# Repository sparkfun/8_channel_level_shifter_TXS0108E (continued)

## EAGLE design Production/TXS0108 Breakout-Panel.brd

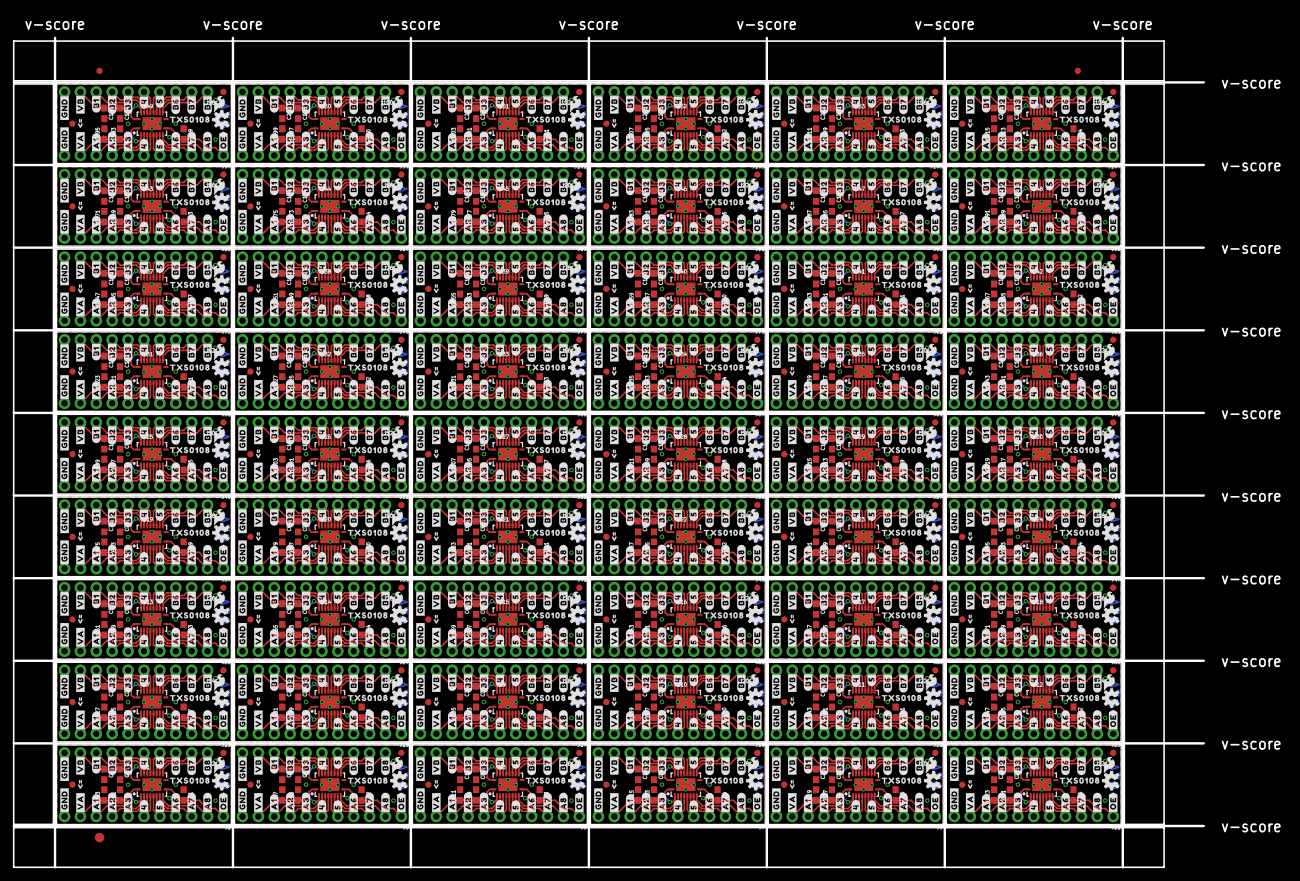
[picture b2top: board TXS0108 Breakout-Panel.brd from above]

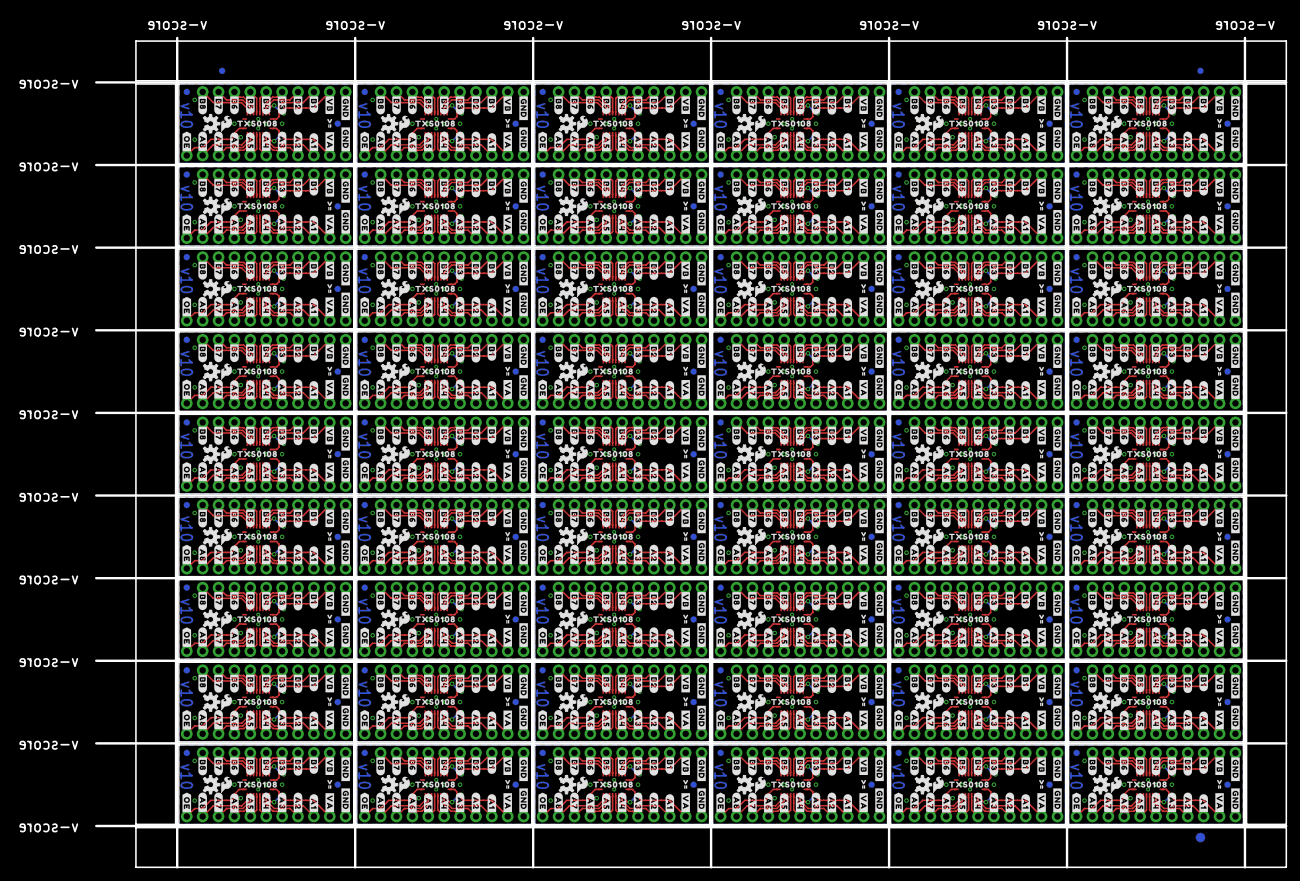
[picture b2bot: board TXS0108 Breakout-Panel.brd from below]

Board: 2 copper layers, 190.2 x 132.6 mm, 3462 parts (1515 on the bottom side), 1080 nets.

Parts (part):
C1, C2, C5, C6, C9, C10, C13, C14, C17, C18, C21, C22, C25, C26, C29, C30, C33, C34, C37, C38, C41, C42, C45, C46, C49, C50, C53, C54, C57, C58, C61, C62, C65, C66, C69, C70, C73, C74, C77, C78, C81, C82, C85, C86, C89, C90, C93, C94, C97, C98, C101, C102, C105, C106, C109, C110, C113, C114, C117, C118, C121, C122, C125, C126, C129, C130, C133, C134, C137, C138, C141, C142, C145, C146, C149, C150, C153, C154, C157, C158, C161, C162, C165, C166, C169, C170, C173, C174, C177, C178, C181, C182, C185, C186, C189, C190, C193, C194, C197, C198, C201, C202, C205, C206, C209, C210, C213, C214: 0.1uF; 0603
C3, C4, C7, C8, C11, C12, C15, C16, C19, C20, C23, C24, C27, C28, C31, C32, C35, C36, C39, C40, C43, C44, C47, C48, C51, C52, C55, C56, C59, C60, C63, C64, C67, C68, C71, C72, C75, C76, C79, C80, C83, C84, C87, C88, C91, C92, C95, C96, C99, C100, C103, C104, C107, C108, C111, C112, C115, C116, C119, C120, C123, C124, C127, C128, C131, C132, C135, C136, C139, C140, C143, C144, C147, C148, C151, C152, C155, C156, C159, C160, C163, C164, C167, C168, C171, C172, C175, C176, C179, C180, C183, C184, C187, C188, C191, C192, C195, C196, C199, C200, C203, C204, C207, C208, C211, C212, C215, C216: 10uF; 0603
E$1, E$2, E$3, E$4: FIDUCIAL-1X2
E$5, E$6: FIDUCIAL-1.5X3
FD1, FD2, FD3, FD4, FD5, FD6, FD7, FD8, FD9, FD10, FD11, FD12, FD13, FD14, FD15, FD16, FD17, FD18, FD19, FD20, FD21, FD22, FD23, FD24, FD25, FD26, FD27, FD28, FD29, FD30, FD31, FD32, FD33, FD34, FD35, FD36, FD37, FD38, FD39, FD40, FD41, FD42, FD43, FD44, FD45, FD46, FD47, FD48, FD49, FD50, FD51, FD52, FD53, FD54, FD55, FD56, FD57, FD58, FD59, FD60, FD61, FD62, FD63, FD64, FD65, FD66, FD67, FD68, FD69, FD70, FD71, FD72, FD73, FD74, FD75, FD76, FD77, FD78, FD79, FD80, FD81, FD82, FD83, FD84, FD85, FD86, FD87, FD88, FD89, FD90, FD91, FD92, FD93, FD94, FD95, FD96, FD97, FD98, FD99, FD100, FD101, FD102, FD103, FD104, FD105, FD106, FD107, FD108, FD109, FD110, FD111, FD112, FD113, FD114, FD115, FD116, FD117, FD118, FD119, FD120, FD121, FD122, FD123, FD124, FD125, FD126, FD127, FD128, FD129, FD130, FD131, FD132, FD133, FD134, FD135, FD136, FD137, FD138, FD139, FD140, FD141, FD142, FD143, FD144, FD145, FD146, FD147, FD148, FD149, FD150, FD151, FD152, FD153, FD154, FD155, FD156, FD157, FD158, FD159, FD160, FD161, FD162, FD163, FD164, FD165, FD166, FD167, FD168, FD169, FD170, FD171, FD172, FD173, FD174, FD175, FD176, FD177, FD178, FD179, FD180, FD181, FD182, FD183, FD184, FD185, FD186, FD187, FD188, FD189, FD190, FD191, FD192, FD193, FD194, FD195, FD196, FD197, FD198, FD199, FD200, FD201, FD202, FD203, FD204, FD205, FD206, FD207, FD208, FD209, FD210, FD211, FD212, FD213, FD214, FD215, FD216: FIDUCIAL1X2; FIDUCIAL-1X2
J1, J3, J5, J7, J9, J11, J13, J15, J17, J19, J21, J23, J25, J27, J29, J31, J33, J35, J37, J39, J41, J43, J45, J47, J49, J51, J53, J55, J57, J59, J61, J63, J65, J67, J69, J71, J73, J75, J77, J79, J81, J83, J85, J87, J89, J91, J93, J95, J97, J99, J101, J103, J105, J107: 1X11_NO_SILK
J2, J4, J6, J8, J10, J12, J14, J16, J18, J20, J22, J24, J26, J28, J30, J32, J34, J36, J38, J40, J42, J44, J46, J48, J50, J52, J54, J56, J58, J60, J62, J64, J66, J68, J70, J72, J74, J76, J78, J80, J82, J84, J86, J88, J90, J92, J94, J96, J98, J100, J102, J104, J106, J108: 1X10_NO_SILK
LOGO1, LOGO4, LOGO5, LOGO8, LOGO9, LOGO12, LOGO13, LOGO16, LOGO17, LOGO20, LOGO21, LOGO24, LOGO25, LOGO28, LOGO29, LOGO32, LOGO33, LOGO36, LOGO37, LOGO40, LOGO41, LOGO44, LOGO45, LOGO48, LOGO49, LOGO52, LOGO53, LOGO56, LOGO57, LOGO60, LOGO61, LOGO64, LOGO65, LOGO68, LOGO69, LOGO72, LOGO73, LOGO76, LOGO77, LOGO80, LOGO81, LOGO84, LOGO85, LOGO88, LOGO89, LOGO92, LOGO93, LOGO96, LOGO97, LOGO100, LOGO101, LOGO104, LOGO105, LOGO108, LOGO109, LOGO112, LOGO113, LOGO116, LOGO117, LOGO120, LOGO121, LOGO124, LOGO125, LOGO128, LOGO129, LOGO132, LOGO133, LOGO136, LOGO137, LOGO140, LOGO141, LOGO144, LOGO145, LOGO148, LOGO149, LOGO152, LOGO153, LOGO156, LOGO157, LOGO160, LOGO161, LOGO164, LOGO165, LOGO168, LOGO169, LOGO172, LOGO173, LOGO176, LOGO177, LOGO180, LOGO181, LOGO184, LOGO185, LOGO188, LOGO189, LOGO192, LOGO193, LOGO196, LOGO197, LOGO200, LOGO201, LOGO204, LOGO205, LOGO208, LOGO209, LOGO212, LOGO213, LOGO216: OSHW-LOGOS; OSHW-LOGO-S
LOGO2, LOGO3, LOGO6, LOGO7, LOGO10, LOGO11, LOGO14, LOGO15, LOGO18, LOGO19, LOGO22, LOGO23, LOGO26, LOGO27, LOGO30, LOGO31, LOGO34, LOGO35, LOGO38, LOGO39, LOGO42, LOGO43, LOGO46, LOGO47, LOGO50, LOGO51, LOGO54, LOGO55, LOGO58, LOGO59, LOGO62, LOGO63, LOGO66, LOGO67, LOGO70, LOGO71, LOGO74, LOGO75, LOGO78, LOGO79, LOGO82, LOGO83, LOGO86, LOGO87, LOGO90, LOGO91, LOGO94, LOGO95, LOGO98, LOGO99, LOGO102, LOGO103, LOGO106, LOGO107, LOGO110, LOGO111, LOGO114, LOGO115, LOGO118, LOGO119, LOGO122, LOGO123, LOGO126, LOGO127, LOGO130, LOGO131, LOGO134, LOGO135, LOGO138, LOGO139, LOGO142, LOGO143, LOGO146, LOGO147, LOGO150, LOGO151, LOGO154, LOGO155, LOGO158, LOGO159, LOGO162, LOGO163, LOGO166, LOGO167, LOGO170, LOGO171, LOGO174, LOGO175, LOGO178, LOGO179, LOGO182, LOGO183, LOGO186, LOGO187, LOGO190, LOGO191, LOGO194, LOGO195, LOGO198, LOGO199, LOGO202, LOGO203, LOGO206, LOGO207, LOGO210, LOGO211, LOGO214, LOGO215: SFE_LOGO_FLAME.1_INCH; SFE_LOGO_FLAME_.1
R1, R2, R3, R4, R5, R6, R7, R8, R9, R10, R11, R12, R13, R14, R15, R16, R17, R18, R19, R20, R21, R22, R23, R24, R25, R26, R27, R28, R29, R30, R31, R32, R33, R34, R35, R36, R37, R38, R39, R40, R41, R42, R43, R44, R45, R46, R47, R48, R49, R50, R51, R52, R53, R54: 100k; 0603
U1, U2, U3, U4, U5, U6, U7, U8, U9, U10, U11, U12, U13, U14, U15, U16, U17, U18, U19, U20, U21, U22, U23, U24, U25, U26, U27, U28, U29, U30, U31, U32, U33, U34, U35, U36, U37, U38, U39, U40, U41, U42, U43, U44, U45, U46, U47, U48, U49, U50, U51, U52, U53, U54: TXS0108; VFQFN-20
U$1, U$2, U$32, U$34, U$49, U$50, U$56, U$57, U$97, U$98, U$104, U$105, U$145, U$146, U$152, U$153, U$193, U$194, U$200, U$201, U$241, U$242, U$248, U$249, U$289, U$290, U$296, U$297, U$337, U$338, U$344, U$345, U$385, U$386, U$392, U$393, U$433, U$434, U$440, U$441, U$481, U$482, U$488, U$489, U$529, U$530, U$536, U$537, U$577, U$578, U$584, U$585, U$625, U$626, U$632, U$633, U$673, U$674, U$680, U$681, U$721, U$722, U$728, U$729, U$769, U$770, U$776, U$777, U$817, U$818, U$824, U$825, U$865, U$866, U$872, U$873, U$913, U$914, U$920, U$921, U$961, U$962, U$968, U$969, U$1009, U$1010, U$1016, U$1017, U$1057, U$1058, U$1064, U$1065, U$1105, U$1106, U$1112, U$1113, U$1153, U$1154, U$1160, U$1161, U$1201, U$1202, U$1208, U$1209, U$1249, U$1250, U$1256, U$1257, U$1297, U$1298, U$1304, U$1305, U$1345, U$1346, U$1352, U$1353, U$1393, U$1394, U$1400, U$1401, U$1441, U$1442, U$1448, U$1449, U$1489, U$1490, U$1496, U$1497, U$1537, U$1538, U$1544, U$1545, U$1585, U$1586, U$1592, U$1593, U$1633, U$1634, U$1640, U$1641, U$1681, U$1682, U$1688, U$1689, U$1729, U$1730, U$1736, U$1737, U$1777, U$1778, U$1784, U$1785, U$1825, U$1826, U$1832, U$1833, U$1873, U$1874, U$1880, U$1881, U$1921, U$1922, U$1928, U$1929, U$1969, U$1970, U$1976, U$1977, U$2017, U$2018, U$2024, U$2025, U$2065, U$2066, U$2072, U$2073, U$2113, U$2114, U$2120, U$2121, U$2161, U$2162, U$2168, U$2169, U$2209, U$2210, U$2216, U$2217, U$2257, U$2258, U$2264, U$2265, U$2305, U$2306, U$2312, U$2313, U$2353, U$2354, U$2360, U$2361, U$2401, U$2402, U$2408, U$2409, U$2449, U$2450, U$2456, U$2457, U$2497, U$2498, U$2504, U$2505, U$2545, U$2546, U$2552, U$2553: #GND#0
U$3, U$4, U$52, U$53, U$100, U$101, U$148, U$149, U$196, U$197, U$244, U$245, U$292, U$293, U$340, U$341, U$388, U$389, U$436, U$437, U$484, U$485, U$532, U$533, U$580, U$581, U$628, U$629, U$676, U$677, U$724, U$725, U$772, U$773, U$820, U$821, U$868, U$869, U$916, U$917, U$964, U$965, U$1012, U$1013, U$1060, U$1061, U$1108, U$1109, U$1156, U$1157, U$1204, U$1205, U$1252, U$1253, U$1300, U$1301, U$1348, U$1349, U$1396, U$1397, U$1444, U$1445, U$1492, U$1493, U$1540, U$1541, U$1588, U$1589, U$1636, U$1637, U$1684, U$1685, U$1732, U$1733, U$1780, U$1781, U$1828, U$1829, U$1876, U$1877, U$1924, U$1925, U$1972, U$1973, U$2020, U$2021, U$2068, U$2069, U$2116, U$2117, U$2164, U$2165, U$2212, U$2213, U$2260, U$2261, U$2308, U$2309, U$2356, U$2357, U$2404, U$2405, U$2452, U$2453, U$2500, U$2501, U$2548, U$2549: #VA#0
U$5, U$60, U$108, U$156, U$204, U$252, U$300, U$348, U$396, U$444, U$492, U$540, U$588, U$636, U$684, U$732, U$780, U$828, U$876, U$924, U$972, U$1020, U$1068, U$1116, U$1164, U$1212, U$1260, U$1308, U$1356, U$1404, U$1452, U$1500, U$1548, U$1596, U$1644, U$1692, U$1740, U$1788, U$1836, U$1884, U$1932, U$1980, U$2028, U$2076, U$2124, U$2172, U$2220, U$2268, U$2316, U$2364, U$2412, U$2460, U$2508, U$2556: #A1#0
U$6, U$61, U$109, U$157, U$205, U$253, U$301, U$349, U$397, U$445, U$493, U$541, U$589, U$637, U$685, U$733, U$781, U$829, U$877, U$925, U$973, U$1021, U$1069, U$1117, U$1165, U$1213, U$1261, U$1309, U$1357, U$1405, U$1453, U$1501, U$1549, U$1597, U$1645, U$1693, U$1741, U$1789, U$1837, U$1885, U$1933, U$1981, U$2029, U$2077, U$2125, U$2173, U$2221, U$2269, U$2317, U$2365, U$2413, U$2461, U$2509, U$2557: #A2#0
U$7, U$62, U$110, U$158, U$206, U$254, U$302, U$350, U$398, U$446, U$494, U$542, U$590, U$638, U$686, U$734, U$782, U$830, U$878, U$926, U$974, U$1022, U$1070, U$1118, U$1166, U$1214, U$1262, U$1310, U$1358, U$1406, U$1454, U$1502, U$1550, U$1598, U$1646, U$1694, U$1742, U$1790, U$1838, U$1886, U$1934, U$1982, U$2030, U$2078, U$2126, U$2174, U$2222, U$2270, U$2318, U$2366, U$2414, U$2462, U$2510, U$2558: #A3#0
U$8, U$93, U$141, U$189, U$237, U$285, U$333, U$381, U$429, U$477, U$525, U$573, U$621, U$669, U$717, U$765, U$813, U$861, U$909, U$957, U$1005, U$1053, U$1101, U$1149, U$1197, U$1245, U$1293, U$1341, U$1389, U$1437, U$1485, U$1533, U$1581, U$1629, U$1677, U$1725, U$1773, U$1821, U$1869, U$1917, U$1965, U$2013, U$2061, U$2109, U$2157, U$2205, U$2253, U$2301, U$2349, U$2397, U$2445, U$2493, U$2541, U$2589: #4#0
U$9, U$94, U$142, U$190, U$238, U$286, U$334, U$382, U$430, U$478, U$526, U$574, U$622, U$670, U$718, U$766, U$814, U$862, U$910, U$958, U$1006, U$1054, U$1102, U$1150, U$1198, U$1246, U$1294, U$1342, U$1390, U$1438, U$1486, U$1534, U$1582, U$1630, U$1678, U$1726, U$1774, U$1822, U$1870, U$1918, U$1966, U$2014, U$2062, U$2110, U$2158, U$2206, U$2254, U$2302, U$2350, U$2398, U$2446, U$2494, U$2542, U$2590: #5#0
U$10, U$63, U$111, U$159, U$207, U$255, U$303, U$351, U$399, U$447, U$495, U$543, U$591, U$639, U$687, U$735, U$783, U$831, U$879, U$927, U$975, U$1023, U$1071, U$1119, U$1167, U$1215, U$1263, U$1311, U$1359, U$1407, U$1455, U$1503, U$1551, U$1599, U$1647, U$1695, U$1743, U$1791, U$1839, U$1887, U$1935, U$1983, U$2031, U$2079, U$2127, U$2175, U$2223, U$2271, U$2319, U$2367, U$2415, U$2463, U$2511, U$2559: #A6#0
U$11, U$64, U$112, U$160, U$208, U$256, U$304, U$352, U$400, U$448, U$496, U$544, U$592, U$640, U$688, U$736, U$784, U$832, U$880, U$928, U$976, U$1024, U$1072, U$1120, U$1168, U$1216, U$1264, U$1312, U$1360, U$1408, U$1456, U$1504, U$1552, U$1600, U$1648, U$1696, U$1744, U$1792, U$1840, U$1888, U$1936, U$1984, U$2032, U$2080, U$2128, U$2176, U$2224, U$2272, U$2320, U$2368, U$2416, U$2464, U$2512, U$2560: #A7#0
U$12, U$65, U$113, U$161, U$209, U$257, U$305, U$353, U$401, U$449, U$497, U$545, U$593, U$641, U$689, U$737, U$785, U$833, U$881, U$929, U$977, U$1025, U$1073, U$1121, U$1169, U$1217, U$1265, U$1313, U$1361, U$1409, U$1457, U$1505, U$1553, U$1601, U$1649, U$1697, U$1745, U$1793, U$1841, U$1889, U$1937, U$1985, U$2033, U$2081, U$2129, U$2177, U$2225, U$2273, U$2321, U$2369, U$2417, U$2465, U$2513, U$2561: #A8#0
U$13, U$66, U$114, U$162, U$210, U$258, U$306, U$354, U$402, U$450, U$498, U$546, U$594, U$642, U$690, U$738, U$786, U$834, U$882, U$930, U$978, U$1026, U$1074, U$1122, U$1170, U$1218, U$1266, U$1314, U$1362, U$1410, U$1458, U$1506, U$1554, U$1602, U$1650, U$1698, U$1746, U$1794, U$1842, U$1890, U$1938, U$1986, U$2034, U$2082, U$2130, U$2178, U$2226, U$2274, U$2322, U$2370, U$2418, U$2466, U$2514, U$2562: #B8#0
U$14, U$67, U$115, U$163, U$211, U$259, U$307, U$355, U$403, U$451, U$499, U$547, U$595, U$643, U$691, U$739, U$787, U$835, U$883, U$931, U$979, U$1027, U$1075, U$1123, U$1171, U$1219, U$1267, U$1315, U$1363, U$1411, U$1459, U$1507, U$1555, U$1603, U$1651, U$1699, U$1747, U$1795, U$1843, U$1891, U$1939, U$1987, U$2035, U$2083, U$2131, U$2179, U$2227, U$2275, U$2323, U$2371, U$2419, U$2467, U$2515, U$2563: #B7#0
U$15, U$68, U$116, U$164, U$212, U$260, U$308, U$356, U$404, U$452, U$500, U$548, U$596, U$644, U$692, U$740, U$788, U$836, U$884, U$932, U$980, U$1028, U$1076, U$1124, U$1172, U$1220, U$1268, U$1316, U$1364, U$1412, U$1460, U$1508, U$1556, U$1604, U$1652, U$1700, U$1748, U$1796, U$1844, U$1892, U$1940, U$1988, U$2036, U$2084, U$2132, U$2180, U$2228, U$2276, U$2324, U$2372, U$2420, U$2468, U$2516, U$2564: #B6#0
U$16, U$95, U$143, U$191, U$239, U$287, U$335, U$383, U$431, U$479, U$527, U$575, U$623, U$671, U$719, U$767, U$815, U$863, U$911, U$959, U$1007, U$1055, U$1103, U$1151, U$1199, U$1247, U$1295, U$1343, U$1391, U$1439, U$1487, U$1535, U$1583, U$1631, U$1679, U$1727, U$1775, U$1823, U$1871, U$1919, U$1967, U$2015, U$2063, U$2111, U$2159, U$2207, U$2255, U$2303, U$2351, U$2399, U$2447, U$2495, U$2543, U$2591: #4#6
U$17, U$96, U$144, U$192, U$240, U$288, U$336, U$384, U$432, U$480, U$528, U$576, U$624, U$672, U$720, U$768, U$816, U$864, U$912, U$960, U$1008, U$1056, U$1104, U$1152, U$1200, U$1248, U$1296, U$1344, U$1392, U$1440, U$1488, U$1536, U$1584, U$1632, U$1680, U$1728, U$1776, U$1824, U$1872, U$1920, U$1968, U$2016, U$2064, U$2112, U$2160, U$2208, U$2256, U$2304, U$2352, U$2400, U$2448, U$2496, U$2544, U$2592: #5#6
U$18, U$69, U$117, U$165, U$213, U$261, U$309, U$357, U$405, U$453, U$501, U$549, U$597, U$645, U$693, U$741, U$789, U$837, U$885, U$933, U$981, U$1029, U$1077, U$1125, U$1173, U$1221, U$1269, U$1317, U$1365, U$1413, U$1461, U$1509, U$1557, U$1605, U$1653, U$1701, U$1749, U$1797, U$1845, U$1893, U$1941, U$1989, U$2037, U$2085, U$2133, U$2181, U$2229, U$2277, U$2325, U$2373, U$2421, U$2469, U$2517, U$2565: #B3#0
U$19, U$70, U$118, U$166, U$214, U$262, U$310, U$358, U$406, U$454, U$502, U$550, U$598, U$646, U$694, U$742, U$790, U$838, U$886, U$934, U$982, U$1030, U$1078, U$1126, U$1174, U$1222, U$1270, U$1318, U$1366, U$1414, U$1462, U$1510, U$1558, U$1606, U$1654, U$1702, U$1750, U$1798, U$1846, U$1894, U$1942, U$1990, U$2038, U$2086, U$2134, U$2182, U$2230, U$2278, U$2326, U$2374, U$2422, U$2470, U$2518, U$2566: #B2#0
U$20, U$71, U$119, U$167, U$215, U$263, U$311, U$359, U$407, U$455, U$503, U$551, U$599, U$647, U$695, U$743, U$791, U$839, U$887, U$935, U$983, U$1031, U$1079, U$1127, U$1175, U$1223, U$1271, U$1319, U$1367, U$1415, U$1463, U$1511, U$1559, U$1607, U$1655, U$1703, U$1751, U$1799, U$1847, U$1895, U$1943, U$1991, U$2039, U$2087, U$2135, U$2183, U$2231, U$2279, U$2327, U$2375, U$2423, U$2471, U$2519, U$2567: #B1#0
U$21, U$51, U$99, U$147, U$195, U$243, U$291, U$339, U$387, U$435, U$483, U$531, U$579, U$627, U$675, U$723, U$771, U$819, U$867, U$915, U$963, U$1011, U$1059, U$1107, U$1155, U$1203, U$1251, U$1299, U$1347, U$1395, U$1443, U$1491, U$1539, U$1587, U$1635, U$1683, U$1731, U$1779, U$1827, U$1875, U$1923, U$1971, U$2019, U$2067, U$2115, U$2163, U$2211, U$2259, U$2307, U$2355, U$2403, U$2451, U$2499, U$2547: #OE#0
U$22, U$23, U$54, U$55, U$102, U$103, U$150, U$151, U$198, U$199, U$246, U$247, U$294, U$295, U$342, U$343, U$390, U$391, U$438, U$439, U$486, U$487, U$534, U$535, U$582, U$583, U$630, U$631, U$678, U$679, U$726, U$727, U$774, U$775, U$822, U$823, U$870, U$871, U$918, U$919, U$966, U$967, U$1014, U$1015, U$1062, U$1063, U$1110, U$1111, U$1158, U$1159, U$1206, U$1207, U$1254, U$1255, U$1302, U$1303, U$1350, U$1351, U$1398, U$1399, U$1446, U$1447, U$1494, U$1495, U$1542, U$1543, U$1590, U$1591, U$1638, U$1639, U$1686, U$1687, U$1734, U$1735, U$1782, U$1783, U$1830, U$1831, U$1878, U$1879, U$1926, U$1927, U$1974, U$1975, U$2022, U$2023, U$2070, U$2071, U$2118, U$2119, U$2166, U$2167, U$2214, U$2215, U$2262, U$2263, U$2310, U$2311, U$2358, U$2359, U$2406, U$2407, U$2454, U$2455, U$2502, U$2503, U$2550, U$2551: #VB#0
U$24, U$72, U$120, U$168, U$216, U$264, U$312, U$360, U$408, U$456, U$504, U$552, U$600, U$648, U$696, U$744, U$792, U$840, U$888, U$936, U$984, U$1032, U$1080, U$1128, U$1176, U$1224, U$1272, U$1320, U$1368, U$1416, U$1464, U$1512, U$1560, U$1608, U$1656, U$1704, U$1752, U$1800, U$1848, U$1896, U$1944, U$1992, U$2040, U$2088, U$2136, U$2184, U$2232, U$2280, U$2328, U$2376, U$2424, U$2472, U$2520, U$2568: #A1#2
U$25, U$73, U$121, U$169, U$217, U$265, U$313, U$361, U$409, U$457, U$505, U$553, U$601, U$649, U$697, U$745, U$793, U$841, U$889, U$937, U$985, U$1033, U$1081, U$1129, U$1177, U$1225, U$1273, U$1321, U$1369, U$1417, U$1465, U$1513, U$1561, U$1609, U$1657, U$1705, U$1753, U$1801, U$1849, U$1897, U$1945, U$1993, U$2041, U$2089, U$2137, U$2185, U$2233, U$2281, U$2329, U$2377, U$2425, U$2473, U$2521, U$2569: #A2#2
U$26, U$74, U$122, U$170, U$218, U$266, U$314, U$362, U$410, U$458, U$506, U$554, U$602, U$650, U$698, U$746, U$794, U$842, U$890, U$938, U$986, U$1034, U$1082, U$1130, U$1178, U$1226, U$1274, U$1322, U$1370, U$1418, U$1466, U$1514, U$1562, U$1610, U$1658, U$1706, U$1754, U$1802, U$1850, U$1898, U$1946, U$1994, U$2042, U$2090, U$2138, U$2186, U$2234, U$2282, U$2330, U$2378, U$2426, U$2474, U$2522, U$2570: #A3#3
U$27, U$75, U$123, U$171, U$219, U$267, U$315, U$363, U$411, U$459, U$507, U$555, U$603, U$651, U$699, U$747, U$795, U$843, U$891, U$939, U$987, U$1035, U$1083, U$1131, U$1179, U$1227, U$1275, U$1323, U$1371, U$1419, U$1467, U$1515, U$1563, U$1611, U$1659, U$1707, U$1755, U$1803, U$1851, U$1899, U$1947, U$1995, U$2043, U$2091, U$2139, U$2187, U$2235, U$2283, U$2331, U$2379, U$2427, U$2475, U$2523, U$2571: #A4#4
U$28, U$76, U$124, U$172, U$220, U$268, U$316, U$364, U$412, U$460, U$508, U$556, U$604, U$652, U$700, U$748, U$796, U$844, U$892, U$940, U$988, U$1036, U$1084, U$1132, U$1180, U$1228, U$1276, U$1324, U$1372, U$1420, U$1468, U$1516, U$1564, U$1612, U$1660, U$1708, U$1756, U$1804, U$1852, U$1900, U$1948, U$1996, U$2044, U$2092, U$2140, U$2188, U$2236, U$2284, U$2332, U$2380, U$2428, U$2476, U$2524, U$2572: #A5#5
U$29, U$77, U$125, U$173, U$221, U$269, U$317, U$365, U$413, U$461, U$509, U$557, U$605, U$653, U$701, U$749, U$797, U$845, U$893, U$941, U$989, U$1037, U$1085, U$1133, U$1181, U$1229, U$1277, U$1325, U$1373, U$1421, U$1469, U$1517, U$1565, U$1613, U$1661, U$1709, U$1757, U$1805, U$1853, U$1901, U$1949, U$1997, U$2045, U$2093, U$2141, U$2189, U$2237, U$2285, U$2333, U$2381, U$2429, U$2477, U$2525, U$2573: #A6#6
U$30, U$78, U$126, U$174, U$222, U$270, U$318, U$366, U$414, U$462, U$510, U$558, U$606, U$654, U$702, U$750, U$798, U$846, U$894, U$942, U$990, U$1038, U$1086, U$1134, U$1182, U$1230, U$1278, U$1326, U$1374, U$1422, U$1470, U$1518, U$1566, U$1614, U$1662, U$1710, U$1758, U$1806, U$1854, U$1902, U$1950, U$1998, U$2046, U$2094, U$2142, U$2190, U$2238, U$2286, U$2334, U$2382, U$2430, U$2478, U$2526, U$2574: #A7#8
U$31, U$79, U$127, U$175, U$223, U$271, U$319, U$367, U$415, U$463, U$511, U$559, U$607, U$655, U$703, U$751, U$799, U$847, U$895, U$943, U$991, U$1039, U$1087, U$1135, U$1183, U$1231, U$1279, U$1327, U$1375, U$1423, U$1471, U$1519, U$1567, U$1615, U$1663, U$1711, U$1759, U$1807, U$1855, U$1903, U$1951, U$1999, U$2047, U$2095, U$2143, U$2191, U$2239, U$2287, U$2335, U$2383, U$2431, U$2479, U$2527, U$2575: #A8#9
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
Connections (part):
A1: J1.9, U1.1
A2: J1.8, U1.3
A3: J1.7, U1.4
A4: J1.6, U1.5
A5: J1.5, U1.6
A6: J1.4, U1.7
A7: J1.3, U1.8
A8: J1.2, U1.9
A9: J3.9, U2.1
A10: J3.8, U2.3
A11: J3.7, U2.4
A12: J3.6, U2.5
A13: J3.5, U2.6
A14: J3.4, U2.7
A15: J3.3, U2.8
A16: J3.2, U2.9
A17: J5.9, U3.1
A18: J5.8, U3.3
A19: J5.7, U3.4
A20: J5.6, U3.5
A21: J5.5, U3.6
A22: J5.4, U3.7
A23: J5.3, U3.8
A24: J5.2, U3.9
A25: J7.9, U4.1
A26: J7.8, U4.3
A27: J7.7, U4.4
A28: J7.6, U4.5
A29: J7.5, U4.6
A30: J7.4, U4.7
A31: J7.3, U4.8
A32: J7.2, U4.9
A33: J9.9, U5.1
A34: J9.8, U5.3
A35: J9.7, U5.4
A36: J9.6, U5.5
A37: J9.5, U5.6
A38: J9.4, U5.7
A39: J9.3, U5.8
A40: J9.2, U5.9
A41: J11.9, U6.1
A42: J11.8, U6.3
A43: J11.7, U6.4
A44: J11.6, U6.5
A45: J11.5, U6.6
A46: J11.4, U6.7
A47: J11.3, U6.8
A48: J11.2, U6.9
A49: J13.9, U7.1
A50: J13.8, U7.3
A51: J13.7, U7.4
A52: J13.6, U7.5
A53: J13.5, U7.6
A54: J13.4, U7.7
A55: J13.3, U7.8
A56: J13.2, U7.9
A57: J15.9, U8.1
A58: J15.8, U8.3
A59: J15.7, U8.4
A60: J15.6, U8.5
A61: J15.5, U8.6
A62: J15.4, U8.7
A63: J15.3, U8.8
A64: J15.2, U8.9
A65: J17.9, U9.1
A66: J17.8, U9.3
A67: J17.7, U9.4
A68: J17.6, U9.5
A69: J17.5, U9.6
A70: J17.4, U9.7
A71: J17.3, U9.8
A72: J17.2, U9.9
A73: J19.9, U10.1
A74: J19.8, U10.3
A75: J19.7, U10.4
A76: J19.6, U10.5
A77: J19.5, U10.6
A78: J19.4, U10.7
A79: J19.3, U10.8
A80: J19.2, U10.9
A81: J21.9, U11.1
A82: J21.8, U11.3
A83: J21.7, U11.4
A84: J21.6, U11.5
A85: J21.5, U11.6
A86: J21.4, U11.7
A87: J21.3, U11.8
A88: J21.2, U11.9
A89: J23.9, U12.1
A90: J23.8, U12.3
A91: J23.7, U12.4
A92: J23.6, U12.5
A93: J23.5, U12.6
A94: J23.4, U12.7
A95: J23.3, U12.8
A96: J23.2, U12.9
A97: J25.9, U13.1
A98: J25.8, U13.3
A99: J25.7, U13.4
A100: J25.6, U13.5
A101: J25.5, U13.6
A102: J25.4, U13.7
A103: J25.3, U13.8
A104: J25.2, U13.9
A105: J27.9, U14.1
A106: J27.8, U14.3
A107: J27.7, U14.4
A108: J27.6, U14.5
A109: J27.5, U14.6
A110: J27.4, U14.7
A111: J27.3, U14.8
A112: J27.2, U14.9
A113: J29.9, U15.1
A114: J29.8, U15.3
A115: J29.7, U15.4
A116: J29.6, U15.5
A117: J29.5, U15.6
A118: J29.4, U15.7
A119: J29.3, U15.8
A120: J29.2, U15.9
A121: J31.9, U16.1
A122: J31.8, U16.3
A123: J31.7, U16.4
A124: J31.6, U16.5
A125: J31.5, U16.6
A126: J31.4, U16.7
A127: J31.3, U16.8
A128: J31.2, U16.9
A129: J33.9, U17.1
A130: J33.8, U17.3
A131: J33.7, U17.4
A132: J33.6, U17.5
A133: J33.5, U17.6
A134: J33.4, U17.7
A135: J33.3, U17.8
A136: J33.2, U17.9
A137: J35.9, U18.1
A138: J35.8, U18.3
A139: J35.7, U18.4
A140: J35.6, U18.5
A141: J35.5, U18.6
A142: J35.4, U18.7
A143: J35.3, U18.8
A144: J35.2, U18.9
A145: J37.9, U19.1
A146: J37.8, U19.3
A147: J37.7, U19.4
A148: J37.6, U19.5
A149: J37.5, U19.6
A150: J37.4, U19.7
A151: J37.3, U19.8
A152: J37.2, U19.9
A153: J39.9, U20.1
A154: J39.8, U20.3
A155: J39.7, U20.4
A156: J39.6, U20.5
A157: J39.5, U20.6
A158: J39.4, U20.7
A159: J39.3, U20.8
A160: J39.2, U20.9
A161: J41.9, U21.1
A162: J41.8, U21.3
A163: J41.7, U21.4
A164: J41.6, U21.5
A165: J41.5, U21.6
A166: J41.4, U21.7
A167: J41.3, U21.8
A168: J41.2, U21.9
A169: J43.9, U22.1
A170: J43.8, U22.3
A171: J43.7, U22.4
A172: J43.6, U22.5
A173: J43.5, U22.6
A174: J43.4, U22.7
A175: J43.3, U22.8
A176: J43.2, U22.9
A177: J45.9, U23.1
A178: J45.8, U23.3
A179: J45.7, U23.4
A180: J45.6, U23.5
A181: J45.5, U23.6
A182: J45.4, U23.7
A183: J45.3, U23.8
A184: J45.2, U23.9
A185: J47.9, U24.1
A186: J47.8, U24.3
A187: J47.7, U24.4
A188: J47.6, U24.5
A189: J47.5, U24.6
A190: J47.4, U24.7
A191: J47.3, U24.8
A192: J47.2, U24.9
A193: J49.9, U25.1
A194: J49.8, U25.3
A195: J49.7, U25.4
A196: J49.6, U25.5
A197: J49.5, U25.6
A198: J49.4, U25.7
A199: J49.3, U25.8
A200: J49.2, U25.9
A201: J51.9, U26.1
A202: J51.8, U26.3
A203: J51.7, U26.4
A204: J51.6, U26.5
A205: J51.5, U26.6
A206: J51.4, U26.7
A207: J51.3, U26.8
A208: J51.2, U26.9
A209: J53.9, U27.1
A210: J53.8, U27.3
A211: J53.7, U27.4
A212: J53.6, U27.5
A213: J53.5, U27.6
A214: J53.4, U27.7
A215: J53.3, U27.8
A216: J53.2, U27.9
A217: J55.9, U28.1
A218: J55.8, U28.3
A219: J55.7, U28.4
A220: J55.6, U28.5
A221: J55.5, U28.6
A222: J55.4, U28.7
A223: J55.3, U28.8
A224: J55.2, U28.9
A225: J57.9, U29.1
A226: J57.8, U29.3
A227: J57.7, U29.4
A228: J57.6, U29.5
A229: J57.5, U29.6
A230: J57.4, U29.7
A231: J57.3, U29.8
A232: J57.2, U29.9
A233: J59.9, U30.1
A234: J59.8, U30.3
A235: J59.7, U30.4
A236: J59.6, U30.5
A237: J59.5, U30.6
A238: J59.4, U30.7
A239: J59.3, U30.8
A240: J59.2, U30.9
A241: J61.9, U31.1
A242: J61.8, U31.3
A243: J61.7, U31.4
A244: J61.6, U31.5
A245: J61.5, U31.6
A246: J61.4, U31.7
A247: J61.3, U31.8
A248: J61.2, U31.9
A249: J63.9, U32.1
A250: J63.8, U32.3
A251: J63.7, U32.4
A252: J63.6, U32.5
A253: J63.5, U32.6
A254: J63.4, U32.7
A255: J63.3, U32.8
A256: J63.2, U32.9
A257: J65.9, U33.1
A258: J65.8, U33.3
A259: J65.7, U33.4
A260: J65.6, U33.5
A261: J65.5, U33.6
A262: J65.4, U33.7
A263: J65.3, U33.8
A264: J65.2, U33.9
A265: J67.9, U34.1
A266: J67.8, U34.3
A267: J67.7, U34.4
A268: J67.6, U34.5
A269: J67.5, U34.6
A270: J67.4, U34.7
A271: J67.3, U34.8
A272: J67.2, U34.9
A273: J69.9, U35.1
A274: J69.8, U35.3
A275: J69.7, U35.4
A276: J69.6, U35.5
A277: J69.5, U35.6
A278: J69.4, U35.7
A279: J69.3, U35.8
A280: J69.2, U35.9
A281: J71.9, U36.1
A282: J71.8, U36.3
A283: J71.7, U36.4
A284: J71.6, U36.5
A285: J71.5, U36.6
A286: J71.4, U36.7
A287: J71.3, U36.8
A288: J71.2, U36.9
A289: J73.9, U37.1
A290: J73.8, U37.3
A291: J73.7, U37.4
A292: J73.6, U37.5
A293: J73.5, U37.6
A294: J73.4, U37.7
A295: J73.3, U37.8
A296: J73.2, U37.9
A297: J75.9, U38.1
A298: J75.8, U38.3
A299: J75.7, U38.4
A300: J75.6, U38.5
A301: J75.5, U38.6
A302: J75.4, U38.7
A303: J75.3, U38.8
A304: J75.2, U38.9
A305: J77.9, U39.1
A306: J77.8, U39.3
A307: J77.7, U39.4
A308: J77.6, U39.5
A309: J77.5, U39.6
A310: J77.4, U39.7
A311: J77.3, U39.8
A312: J77.2, U39.9
A313: J79.9, U40.1
A314: J79.8, U40.3
A315: J79.7, U40.4
A316: J79.6, U40.5
A317: J79.5, U40.6
A318: J79.4, U40.7
A319: J79.3, U40.8
A320: J79.2, U40.9
A321: J81.9, U41.1
A322: J81.8, U41.3
A323: J81.7, U41.4
A324: J81.6, U41.5
A325: J81.5, U41.6
A326: J81.4, U41.7
A327: J81.3, U41.8
A328: J81.2, U41.9
A329: J83.9, U42.1
A330: J83.8, U42.3
A331: J83.7, U42.4
A332: J83.6, U42.5
A333: J83.5, U42.6
A334: J83.4, U42.7
A335: J83.3, U42.8
A336: J83.2, U42.9
A337: J85.9, U43.1
A338: J85.8, U43.3
A339: J85.7, U43.4
A340: J85.6, U43.5
A341: J85.5, U43.6
A342: J85.4, U43.7
A343: J85.3, U43.8
A344: J85.2, U43.9
A345: J87.9, U44.1
A346: J87.8, U44.3
A347: J87.7, U44.4
A348: J87.6, U44.5
A349: J87.5, U44.6
A350: J87.4, U44.7
A351: J87.3, U44.8
A352: J87.2, U44.9
A353: J89.9, U45.1
A354: J89.8, U45.3
A355: J89.7, U45.4
A356: J89.6, U45.5
A357: J89.5, U45.6
A358: J89.4, U45.7
A359: J89.3, U45.8
A360: J89.2, U45.9
A361: J91.9, U46.1
A362: J91.8, U46.3
A363: J91.7, U46.4
A364: J91.6, U46.5
A365: J91.5, U46.6
A366: J91.4, U46.7
A367: J91.3, U46.8
A368: J91.2, U46.9
A369: J93.9, U47.1
A370: J93.8, U47.3
A371: J93.7, U47.4
A372: J93.6, U47.5
A373: J93.5, U47.6
A374: J93.4, U47.7
A375: J93.3, U47.8
A376: J93.2, U47.9
A377: J95.9, U48.1
A378: J95.8, U48.3
A379: J95.7, U48.4
A380: J95.6, U48.5
A381: J95.5, U48.6
A382: J95.4, U48.7
A383: J95.3, U48.8
A384: J95.2, U48.9
A385: J97.9, U49.1
A386: J97.8, U49.3
A387: J97.7, U49.4
A388: J97.6, U49.5
A389: J97.5, U49.6
A390: J97.4, U49.7
A391: J97.3, U49.8
A392: J97.2, U49.9
A393: J99.9, U50.1
A394: J99.8, U50.3
A395: J99.7, U50.4
A396: J99.6, U50.5
A397: J99.5, U50.6
A398: J99.4, U50.7
A399: J99.3, U50.8
A400: J99.2, U50.9
A401: J101.9, U51.1
A402: J101.8, U51.3
A403: J101.7, U51.4
A404: J101.6, U51.5
A405: J101.5, U51.6
A406: J101.4, U51.7
A407: J101.3, U51.8
A408: J101.2, U51.9
A409: J103.9, U52.1
A410: J103.8, U52.3
A411: J103.7, U52.4
A412: J103.6, U52.5
A413: J103.5, U52.6
A414: J103.4, U52.7
A415: J103.3, U52.8
A416: J103.2, U52.9
A417: J105.9, U53.1
A418: J105.8, U53.3
A419: J105.7, U53.4
A420: J105.6, U53.5
A421: J105.5, U53.6
A422: J105.4, U53.7
A423: J105.3, U53.8
A424: J105.2, U53.9
A425: J107.9, U54.1
A426: J107.8, U54.3
A427: J107.7, U54.4
A428: J107.6, U54.5
A429: J107.5, U54.6
A430: J107.4, U54.7
A431: J107.3, U54.8
A432: J107.2, U54.9
B1: J2.8, U1.20
B2: J2.7, U1.18
B3: J2.6, U1.17
B4: J2.5, U1.16
B5: J2.4, U1.15
B6: J2.3, U1.14
B7: J2.2, U1.13
B8: J2.1, U1.12
B9: J4.8, U2.20
B10: J4.7, U2.18
B11: J4.6, U2.17
B12: J4.5, U2.16
B13: J4.4, U2.15
B14: J4.3, U2.14
B15: J4.2, U2.13
B16: J4.1, U2.12
B17: J6.8, U3.20
B18: J6.7, U3.18
B19: J6.6, U3.17
B20: J6.5, U3.16
B21: J6.4, U3.15
B22: J6.3, U3.14
B23: J6.2, U3.13
B24: J6.1, U3.12
B25: J8.8, U4.20
B26: J8.7, U4.18
B27: J8.6, U4.17
B28: J8.5, U4.16
B29: J8.4, U4.15
B30: J8.3, U4.14
B31: J8.2, U4.13
B32: J8.1, U4.12
B33: J10.8, U5.20
B34: J10.7, U5.18
B35: J10.6, U5.17
B36: J10.5, U5.16
B37: J10.4, U5.15
B38: J10.3, U5.14
B39: J10.2, U5.13
B40: J10.1, U5.12
B41: J12.8, U6.20
B42: J12.7, U6.18
B43: J12.6, U6.17
B44: J12.5, U6.16
B45: J12.4, U6.15
B46: J12.3, U6.14
B47: J12.2, U6.13
B48: J12.1, U6.12
B49: J14.8, U7.20
B50: J14.7, U7.18
B51: J14.6, U7.17
B52: J14.5, U7.16
B53: J14.4, U7.15
B54: J14.3, U7.14
B55: J14.2, U7.13
B56: J14.1, U7.12
B57: J16.8, U8.20
B58: J16.7, U8.18
B59: J16.6, U8.17
B60: J16.5, U8.16
B61: J16.4, U8.15
B62: J16.3, U8.14
B63: J16.2, U8.13
B64: J16.1, U8.12
B65: J18.8, U9.20
B66: J18.7, U9.18
B67: J18.6, U9.17
B68: J18.5, U9.16
B69: J18.4, U9.15
B70: J18.3, U9.14
B71: J18.2, U9.13
B72: J18.1, U9.12
B73: J20.8, U10.20
B74: J20.7, U10.18
B75: J20.6, U10.17
B76: J20.5, U10.16
B77: J20.4, U10.15
B78: J20.3, U10.14
B79: J20.2, U10.13
B80: J20.1, U10.12
B81: J22.8, U11.20
B82: J22.7, U11.18
B83: J22.6, U11.17
B84: J22.5, U11.16
B85: J22.4, U11.15
B86: J22.3, U11.14
B87: J22.2, U11.13
B88: J22.1, U11.12
B89: J24.8, U12.20
B90: J24.7, U12.18
B91: J24.6, U12.17
B92: J24.5, U12.16
B93: J24.4, U12.15
B94: J24.3, U12.14
B95: J24.2, U12.13
B96: J24.1, U12.12
B97: J26.8, U13.20
B98: J26.7, U13.18
B99: J26.6, U13.17
B100: J26.5, U13.16
B101: J26.4, U13.15
B102: J26.3, U13.14
B103: J26.2, U13.13
B104: J26.1, U13.12
B105: J28.8, U14.20
B106: J28.7, U14.18
B107: J28.6, U14.17
B108: J28.5, U14.16
B109: J28.4, U14.15
B110: J28.3, U14.14
B111: J28.2, U14.13
B112: J28.1, U14.12
B113: J30.8, U15.20
B114: J30.7, U15.18
B115: J30.6, U15.17
B116: J30.5, U15.16
B117: J30.4, U15.15
B118: J30.3, U15.14
B119: J30.2, U15.13
B120: J30.1, U15.12
B121: J32.8, U16.20
B122: J32.7, U16.18
B123: J32.6, U16.17
B124: J32.5, U16.16
B125: J32.4, U16.15
B126: J32.3, U16.14
B127: J32.2, U16.13
B128: J32.1, U16.12
B129: J34.8, U17.20
B130: J34.7, U17.18
B131: J34.6, U17.17
B132: J34.5, U17.16
B133: J34.4, U17.15
B134: J34.3, U17.14
B135: J34.2, U17.13
B136: J34.1, U17.12
B137: J36.8, U18.20
B138: J36.7, U18.18
B139: J36.6, U18.17
B140: J36.5, U18.16
B141: J36.4, U18.15
B142: J36.3, U18.14
B143: J36.2, U18.13
B144: J36.1, U18.12
B145: J38.8, U19.20
B146: J38.7, U19.18
B147: J38.6, U19.17
B148: J38.5, U19.16
B149: J38.4, U19.15
B150: J38.3, U19.14
B151: J38.2, U19.13
B152: J38.1, U19.12
B153: J40.8, U20.20
B154: J40.7, U20.18
B155: J40.6, U20.17
B156: J40.5, U20.16
B157: J40.4, U20.15
B158: J40.3, U20.14
B159: J40.2, U20.13
B160: J40.1, U20.12
B161: J42.8, U21.20
B162: J42.7, U21.18
B163: J42.6, U21.17
B164: J42.5, U21.16
B165: J42.4, U21.15
B166: J42.3, U21.14
B167: J42.2, U21.13
B168: J42.1, U21.12
B169: J44.8, U22.20
B170: J44.7, U22.18
B171: J44.6, U22.17
B172: J44.5, U22.16
B173: J44.4, U22.15
B174: J44.3, U22.14
B175: J44.2, U22.13
B176: J44.1, U22.12
B177: J46.8, U23.20
B178: J46.7, U23.18
B179: J46.6, U23.17
B180: J46.5, U23.16
B181: J46.4, U23.15
B182: J46.3, U23.14
B183: J46.2, U23.13
B184: J46.1, U23.12
B185: J48.8, U24.20
B186: J48.7, U24.18
B187: J48.6, U24.17
B188: J48.5, U24.16
B189: J48.4, U24.15
B190: J48.3, U24.14
B191: J48.2, U24.13
B192: J48.1, U24.12
B193: J50.8, U25.20
B194: J50.7, U25.18
B195: J50.6, U25.17
B196: J50.5, U25.16
B197: J50.4, U25.15
B198: J50.3, U25.14
B199: J50.2, U25.13
B200: J50.1, U25.12
B201: J52.8, U26.20
B202: J52.7, U26.18
B203: J52.6, U26.17
B204: J52.5, U26.16
B205: J52.4, U26.15
B206: J52.3, U26.14
B207: J52.2, U26.13
B208: J52.1, U26.12
B209: J54.8, U27.20
B210: J54.7, U27.18
B211: J54.6, U27.17
B212: J54.5, U27.16
B213: J54.4, U27.15
B214: J54.3, U27.14
B215: J54.2, U27.13
B216: J54.1, U27.12
B217: J56.8, U28.20
B218: J56.7, U28.18
B219: J56.6, U28.17
B220: J56.5, U28.16
B221: J56.4, U28.15
B222: J56.3, U28.14
B223: J56.2, U28.13
B224: J56.1, U28.12
B225: J58.8, U29.20
B226: J58.7, U29.18
B227: J58.6, U29.17
B228: J58.5, U29.16
B229: J58.4, U29.15
B230: J58.3, U29.14
B231: J58.2, U29.13
B232: J58.1, U29.12
B233: J60.8, U30.20
B234: J60.7, U30.18
B235: J60.6, U30.17
B236: J60.5, U30.16
B237: J60.4, U30.15
B238: J60.3, U30.14
B239: J60.2, U30.13
B240: J60.1, U30.12
B241: J62.8, U31.20
B242: J62.7, U31.18
B243: J62.6, U31.17
B244: J62.5, U31.16
B245: J62.4, U31.15
B246: J62.3, U31.14
B247: J62.2, U31.13
B248: J62.1, U31.12
B249: J64.8, U32.20
B250: J64.7, U32.18
B251: J64.6, U32.17
B252: J64.5, U32.16
B253: J64.4, U32.15
B254: J64.3, U32.14
B255: J64.2, U32.13
B256: J64.1, U32.12
B257: J66.8, U33.20
B258: J66.7, U33.18
B259: J66.6, U33.17
B260: J66.5, U33.16
B261: J66.4, U33.15
B262: J66.3, U33.14
B263: J66.2, U33.13
B264: J66.1, U33.12
B265: J68.8, U34.20
B266: J68.7, U34.18
B267: J68.6, U34.17
B268: J68.5, U34.16
B269: J68.4, U34.15
B270: J68.3, U34.14
B271: J68.2, U34.13
B272: J68.1, U34.12
B273: J70.8, U35.20
B274: J70.7, U35.18
B275: J70.6, U35.17
B276: J70.5, U35.16
B277: J70.4, U35.15
B278: J70.3, U35.14
B279: J70.2, U35.13
B280: J70.1, U35.12
B281: J72.8, U36.20
B282: J72.7, U36.18
B283: J72.6, U36.17
B284: J72.5, U36.16
B285: J72.4, U36.15
B286: J72.3, U36.14
B287: J72.2, U36.13
B288: J72.1, U36.12
B289: J74.8, U37.20
B290: J74.7, U37.18
B291: J74.6, U37.17
B292: J74.5, U37.16
B293: J74.4, U37.15
B294: J74.3, U37.14
B295: J74.2, U37.13
B296: J74.1, U37.12
B297: J76.8, U38.20
B298: J76.7, U38.18
B299: J76.6, U38.17
B300: J76.5, U38.16
B301: J76.4, U38.15
B302: J76.3, U38.14
B303: J76.2, U38.13
B304: J76.1, U38.12
B305: J78.8, U39.20
B306: J78.7, U39.18
B307: J78.6, U39.17
B308: J78.5, U39.16
B309: J78.4, U39.15
B310: J78.3, U39.14
B311: J78.2, U39.13
B312: J78.1, U39.12
B313: J80.8, U40.20
B314: J80.7, U40.18
B315: J80.6, U40.17
B316: J80.5, U40.16
B317: J80.4, U40.15
B318: J80.3, U40.14
B319: J80.2, U40.13
B320: J80.1, U40.12
B321: J82.8, U41.20
B322: J82.7, U41.18
B323: J82.6, U41.17
B324: J82.5, U41.16
B325: J82.4, U41.15
B326: J82.3, U41.14
B327: J82.2, U41.13
B328: J82.1, U41.12
B329: J84.8, U42.20
B330: J84.7, U42.18
B331: J84.6, U42.17
B332: J84.5, U42.16
B333: J84.4, U42.15
B334: J84.3, U42.14
B335: J84.2, U42.13
B336: J84.1, U42.12
B337: J86.8, U43.20
B338: J86.7, U43.18
B339: J86.6, U43.17
B340: J86.5, U43.16
B341: J86.4, U43.15
B342: J86.3, U43.14
B343: J86.2, U43.13
B344: J86.1, U43.12
B345: J88.8, U44.20
B346: J88.7, U44.18
B347: J88.6, U44.17
B348: J88.5, U44.16
B349: J88.4, U44.15
B350: J88.3, U44.14
B351: J88.2, U44.13
B352: J88.1, U44.12
B353: J90.8, U45.20
B354: J90.7, U45.18
B355: J90.6, U45.17
B356: J90.5, U45.16
B357: J90.4, U45.15
B358: J90.3, U45.14
B359: J90.2, U45.13
B360: J90.1, U45.12
B361: J92.8, U46.20
B362: J92.7, U46.18
B363: J92.6, U46.17
B364: J92.5, U46.16
B365: J92.4, U46.15
B366: J92.3, U46.14
B367: J92.2, U46.13
B368: J92.1, U46.12
B369: J94.8, U47.20
B370: J94.7, U47.18
B371: J94.6, U47.17
B372: J94.5, U47.16
B373: J94.4, U47.15
B374: J94.3, U47.14
B375: J94.2, U47.13
B376: J94.1, U47.12
B377: J96.8, U48.20
B378: J96.7, U48.18
B379: J96.6, U48.17
B380: J96.5, U48.16
B381: J96.4, U48.15
B382: J96.3, U48.14
B383: J96.2, U48.13
B384: J96.1, U48.12
B385: J98.8, U49.20
B386: J98.7, U49.18
B387: J98.6, U49.17
B388: J98.5, U49.16
B389: J98.4, U49.15
B390: J98.3, U49.14
B391: J98.2, U49.13
B392: J98.1, U49.12
B393: J100.8, U50.20
B394: J100.7, U50.18
B395: J100.6, U50.17
B396: J100.5, U50.16
B397: J100.4, U50.15
B398: J100.3, U50.14
B399: J100.2, U50.13
B400: J100.1, U50.12
B401: J102.8, U51.20
B402: J102.7, U51.18
B403: J102.6, U51.17
B404: J102.5, U51.16
B405: J102.4, U51.15
B406: J102.3, U51.14
B407: J102.2, U51.13
B408: J102.1, U51.12
B409: J104.8, U52.20
B410: J104.7, U52.18
B411: J104.6, U52.17
B412: J104.5, U52.16
B413: J104.4, U52.15
B414: J104.3, U52.14
B415: J104.2, U52.13
B416: J104.1, U52.12
B417: J106.8, U53.20
B418: J106.7, U53.18
B419: J106.6, U53.17
B420: J106.5, U53.16
B421: J106.4, U53.15
B422: J106.3, U53.14
B423: J106.2, U53.13
B424: J106.1, U53.12
B425: J108.8, U54.20
B426: J108.7, U54.18
B427: J108.6, U54.17
B428: J108.5, U54.16
B429: J108.4, U54.15
B430: J108.3, U54.14
B431: J108.2, U54.13
B432: J108.1, U54.12
GND: C1.2, C2.2, C3.2, C4.2, J1.11, J2.10, R1.1, U1.11, U1.EPAD
GND1: C5.2, C6.2, C7.2, C8.2, J3.11, J4.10, R2.1, U2.11, U2.EPAD
GND2: C9.2, C10.2, C11.2, C12.2, J5.11, J6.10, R3.1, U3.11, U3.EPAD
GND3: C13.2, C14.2, C15.2, C16.2, J7.11, J8.10, R4.1, U4.11, U4.EPAD
GND4: C17.2, C18.2, C19.2, C20.2, J9.11, J10.10, R5.1, U5.11, U5.EPAD
GND5: C21.2, C22.2, C23.2, C24.2, J11.11, J12.10, R6.1, U6.11, U6.EPAD
GND6: C25.2, C26.2, C27.2, C28.2, J13.11, J14.10, R7.1, U7.11, U7.EPAD
GND7: C29.2, C30.2, C31.2, C32.2, J15.11, J16.10, R8.1, U8.11, U8.EPAD
GND8: C33.2, C34.2, C35.2, C36.2, J17.11, J18.10, R9.1, U9.11, U9.EPAD
GND9: C37.2, C38.2, C39.2, C40.2, J19.11, J20.10, R10.1, U10.11, U10.EPAD
GND10: C41.2, C42.2, C43.2, C44.2, J21.11, J22.10, R11.1, U11.11, U11.EPAD
GND11: C45.2, C46.2, C47.2, C48.2, J23.11, J24.10, R12.1, U12.11, U12.EPAD
GND12: C49.2, C50.2, C51.2, C52.2, J25.11, J26.10, R13.1, U13.11, U13.EPAD
GND13: C53.2, C54.2, C55.2, C56.2, J27.11, J28.10, R14.1, U14.11, U14.EPAD
GND14: C57.2, C58.2, C59.2, C60.2, J29.11, J30.10, R15.1, U15.11, U15.EPAD
GND15: C61.2, C62.2, C63.2, C64.2, J31.11, J32.10, R16.1, U16.11, U16.EPAD
GND16: C65.2, C66.2, C67.2, C68.2, J33.11, J34.10, R17.1, U17.11, U17.EPAD
GND17: C69.2, C70.2, C71.2, C72.2, J35.11, J36.10, R18.1, U18.11, U18.EPAD
GND18: C73.2, C74.2, C75.2, C76.2, J37.11, J38.10, R19.1, U19.11, U19.EPAD
GND19: C77.2, C78.2, C79.2, C80.2, J39.11, J40.10, R20.1, U20.11, U20.EPAD
GND20: C81.2, C82.2, C83.2, C84.2, J41.11, J42.10, R21.1, U21.11, U21.EPAD
GND21: C85.2, C86.2, C87.2, C88.2, J43.11, J44.10, R22.1, U22.11, U22.EPAD
GND22: C89.2, C90.2, C91.2, C92.2, J45.11, J46.10, R23.1, U23.11, U23.EPAD
GND23: C93.2, C94.2, C95.2, C96.2, J47.11, J48.10, R24.1, U24.11, U24.EPAD
GND24: C97.2, C98.2, C99.2, C100.2, J49.11, J50.10, R25.1, U25.11, U25.EPAD
GND25: C101.2, C102.2, C103.2, C104.2, J51.11, J52.10, R26.1, U26.11, U26.EPAD
GND26: C105.2, C106.2, C107.2, C108.2, J53.11, J54.10, R27.1, U27.11, U27.EPAD
GND27: C109.2, C110.2, C111.2, C112.2, J55.11, J56.10, R28.1, U28.11, U28.EPAD
GND28: C113.2, C114.2, C115.2, C116.2, J57.11, J58.10, R29.1, U29.11, U29.EPAD
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
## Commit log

2022-03-24 First Board Prototype
2022-03-28 Design review revision
2022-03-28 Final Proto Tweaks
    Added GND vias
    Added units to measures
2022-03-28 Proto Gerber files
2022-03-31 Add panelization v10
2022-04-01 Add datasheet
2022-05-17 Update README.md
    Adding README.md file following SFE template in preparation for release.
2023-10-23 Update README.md
    Update tutorial link
